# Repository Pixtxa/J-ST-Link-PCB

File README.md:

# J-ST-Link-PCB
Adapter PCB for connecting a programmer (SEGGER J-Link or STMicroelectronics ST-Link) to a microcontroller via jumper cables or 10 pin header.
It's also possible to monitor the target supply by LED or supply the target (with voltage regulator) or do both, when a 3 way jumper is used.
Because of this, Vtarget is called VCC.

<br>

## Schematic

## Components
Not all components are needed.
Some footprints can be used in multiple ways.
Some options cancel out each other.

Plan and solder what you need for your case.

### Examples

When using a keyed 20-pin female header, it fits nicely on J-Link base and ST-Link/V2.
A 6-pin female header can be soldered on the side to also support the nucleo ST-Link boards and it will still nicely fit on the J-Link Base, but not so nice on the ST-Link/V2.
Instead of the 20-pin female header, a male connector can be used. In this case (or if completely unused) it's possible to solder the Nucleo connector straight down.
It's only needed to solter the parts for the needed paths.
If the 3.3V regulator is unused (ST-Link provides 3.3 V; some targets are compatible with 5 V from J-Link), there is a solder jumper where the regulator would sit to bypass the pad.
Some other connecors are also avialable as female version; there are also angled connectors that might be better for some applications.
The pinout of the 10 pin connectors can be modified by some solder jumpers.
When ordering PCBs you mostly will get some more for a cheap price, so I reccomend to assemble different versions for different applications and maybe use different colored parts.

### Connectors
- 20 pin header
  - For standard ST-Link or J-Link
  - Can be soldered as male connector on top side for connecting to a cable
  - Can be soldered as female connector on bottom side for connecting directly to the programmer
    - PCB dimensions are designed for this usage with ST-Link/V2 and J-Link Base
    - I've found them as [2.54 mm pitch 20 pin female header with polarizing key, wide type on AliExpress](https://www.aliexpress.com/item/32956131069.html?spm=a2g0o.order_list.order_list_main.14.36e81802jonIUv)
  - Pinout is mostly [JTAG Interface Connection](https://www.segger.com/products/debug-probes/j-link/technology/interface-description/) with changes for ST-Link:
    - Pin 1+2: Bridged together (some ST-Link need both wired together for cable detection or something while pin 2 is unused on J-Link, so connecting them seems fine)
    - Pin 4: UART RX (ST-Link)
    - Pin 6: UART TX (ST-Link)
    - Pin 8: Boot0 (ST-Link)
    - Pin 10: SWIM (ST-Link)
    - Pin 14: SWIM_nRST (ST-Link)
- 6 pin header
  - Designed to be compatible with [CN4 of the break away ST-Link on STM32 nucleo boards](https://ehelectronics.wordpress.com/2015/12/05/stm32-nucleo-and-st-link/)
  - Can be soldered straight down to sit nicely above the Nucleo ST-Link
  - Can be soldered to the side to be combined with the 20 pin female header and will still fit nicely on the J-Link base
  - Pin 1-4 can be used with pogo pins [for programming hoverboards (SWD Programming Header)](https://github.com/lucysrausch/hoverboard-firmware-hack)
- Two 10 pin headers
  - 1.27 mm pitch version for connecting directly to my targets
    - I've found them as [1.27mm pitch SMD male shrouded box header on AliExpress](https://www.aliexpress.com/item/32951697063.html?spm=a2g0o.order_list.order_list_main.40.36e81802jonIUv) and [on Mouser](https://my.mouser.com/ProductDetail/Amphenol-FCI/20021521-00010C1LF?qs=pLQRQR43dtoQtFgybK4DSw%3D%3D)
  - 2.54 mm pitch version for other targets, Tag connect or other adapters
  - Both connectors share the same pinout
    - It's designed to be compatible with [the PCB-side connector of the 10-Pin Needle Adapter](https://www.segger.com/products/debug-probes/j-link/accessories/adapters/10-pin-needle-adapter/) and ARM 10 pin JTAG/SWD
    - Pin 5, 7 and 9 are [configurable via solder jumpers](https://github.com/Pixtxa/J-ST-Link-PCB#jumpers)
- Three pin headers on top
  - Can be used for connecting jumper cables
  - Can be used to solder wires directly on
  - STM8 SWIM
    - For SWIM programming with ST-LINK/V1, maybe also /V2
    - Used by STM8 microcontrollers
    - Implemented but untested
  - STM32 SWD
    - For SWD programming with J-Link and ST-Link
    - Used by STM32 Microcontrollers
  - UART
    - ST-Link features UART somehow, so this might be interesting for debugging or programming ESP8266 or ESP32
    - Implemented but untested

### Jumpers
- J1
  - NC*: Don't monitor/supply VCC - VCC is only connected to the programmer
  - LEFT+MIDDLE: Monitor VCC - VCC is connected to the programmer and an LED (if LED + resistor is assembled)
  - MIDDLE+RIGHT: Supply VCC - VCC is connected to the programmer and the supply voltage (if voltage regulator is assembled or J3 is set)
  - LEFT+MIDDLE+RIGHT: Monitor and supply VCC - combination of the last two options above
- J3
  - NC*: Use voltage regulator for supply voltage
  - SET: Skip voltage regulator, wire Pin 19 (5 V on J-Link; 3.3 V on ST-Link) directly to J1
- J5
  - CON*: Connect Supply to pin 5
  - NC: Not connect anything to pin 5
  - GNC: Connect Ground to pin 5
- J7
  - CON*: Connect RTCK to pin 7
  - NC: Not connect anything to pin 7
  - GNC: Connect Ground to pin 7
- J9
  - CON*: Connect nTrst to pin 9
  - NC: Not connect anything to pin 9
  - GNC: Connect Ground to pin 9
* = default

### LED + Resistor
- Only lights up if J1 is selected to monitor VCC and there is voltage on VCC
- Both 0603
- LED color doesn't really matter, chose what you like, but make sure it works with your target voltage (usualy red works with lowest voltage)
- Resistor value depends on LED and target voltage, but 330...1000 Ω should be fine for most LEDs

### Voltage regulator + capacitors
- Designed for 3.3 V via TLV70433 with 100n 0603 capacitors
- Only needed for powering 3.3 V targets on J-Link, which outputs 5 V
  - ST-Link already outputs 3.3 V and doesn't need it
  - Because of TLV70433 has a low voltage drop, it's possible for most 3.3 V targets to assemble the regulator and use this PCB on J-Link and ST-Link 
- Other voltage regulators (second source or for other voltage levels) might be compatible with this footprint
- If unused, J3 (located whrere the regulator would sit) can be set to bypass the regulator pad

## Tested
- Programmers
  - J-Link Base (SWD)
  - ST-Link/V2 (SWD)
- Microcontrollers
  - STM32C0 (SWD)
  - STM32F1 (SWD)
  - STM32L0 (SWD)
- Target Connectors
  - STM32 (SWD)
  - 10 pin 1.27 mm (SWD)
  - 10 pin 2.54 mm (SWD)

## Attribution
- Adafruit microbuilder and built in EAGLE libs are used together with own changes/modifications
- [EAGLE.gitignore by github](https://github.com/github/gitignore/blob/main/Eagle.gitignore)

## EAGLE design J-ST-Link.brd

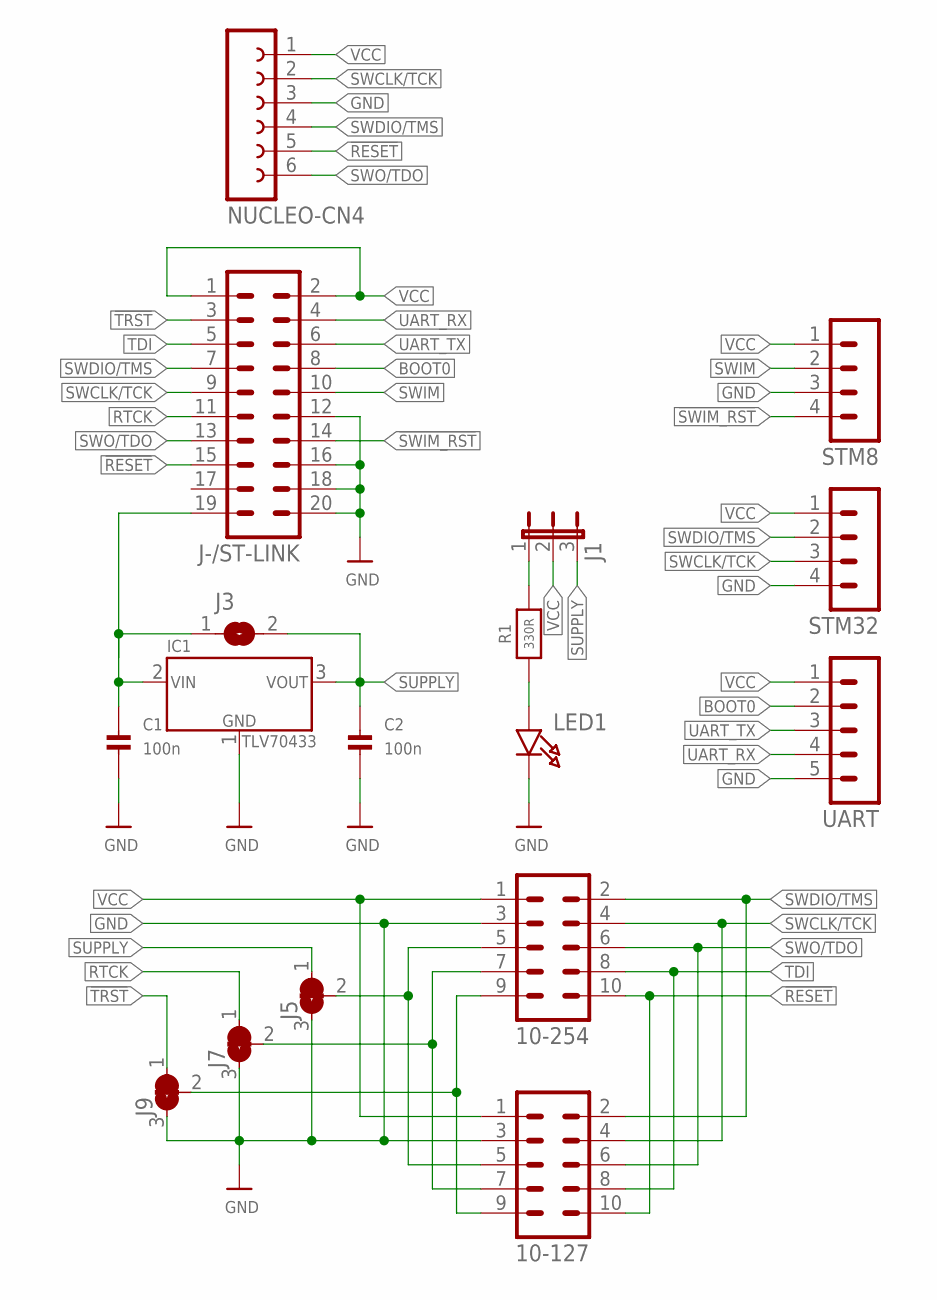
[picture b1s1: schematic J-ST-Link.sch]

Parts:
10-127: CON-HARTING-ML_ML10S
10-254: ML10
C1, C2: 100n; _0603MP
IC1: TLV70433; SOT23-5
J1: JUMPER3LONG; JUMPER3_LONG
J3: SOLDERJUMPERSMALL_NOPRINT; SOLDERJUMPER_SMALL_NOPRINT
J5, J7, J9: SOLDERJUMPER_2WAY_CLOSED; SOLDERJUMPER_2WAY_CLOSED_0603
J-/ST-LINK: ML20
LED1: LED0603_NOOUTLINE; CHIPLED_0603_NOOUTLINE
NUCLEO-CN4: FE06WSQUARE; FE06W_SQUARE
R1: 330R; 0603-NO
STM8, STM32: MA04-1
UART: MA05-1

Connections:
!RESET: 10-127.10, 10-254.10, J-/ST-LINK.15, NUCLEO-CN4.5
!SWIM_RST: J-/ST-LINK.14, STM8.4
!TRST: J9.1, J-/ST-LINK.3
BOOT0: J-/ST-LINK.8, UART.2
GND: 10-127.3, 10-254.3, C1.2, C2.2, IC1.1 (GND), J5.3, J7.3, J9.3, J-/ST-LINK.12, J-/ST-LINK.16, J-/ST-LINK.18, J-/ST-LINK.20, LED1.C, NUCLEO-CN4.3, STM8.3, STM32.4, UART.5
unnamed: LED1.A, R1.1
unnamed: J1.1, R1.2
RTCK: J7.1, J-/ST-LINK.11
RTCK/NC/GND: 10-127.7, 10-254.7, J7.2
SUPPLY: C2.1, IC1.3 (OUT), J1.3, J3.2, J5.1
SUPPLY/NC/GND: 10-127.5, 10-254.5, J5.2
SUPPLY_IN: C1.1, IC1.2 (IN), J3.1, J-/ST-LINK.19
SWCLK/TCK: 10-127.4, 10-254.4, J-/ST-LINK.9, NUCLEO-CN4.2, STM32.3
SWDIO/TMS: 10-127.2, 10-254.2, J-/ST-LINK.7, NUCLEO-CN4.4, STM32.2
SWIM: J-/ST-LINK.10, STM8.2
SWO/TDO: 10-127.6, 10-254.6, J-/ST-LINK.13, NUCLEO-CN4.6
TDI: 10-127.8, 10-254.8, J-/ST-LINK.5
TRST/NC/GND: 10-127.9, 10-254.9, J9.2
UART_RX: J-/ST-LINK.4, UART.4
UART_TX: J-/ST-LINK.6, UART.3
VCC: 10-127.1, 10-254.1, J1.2, J-/ST-LINK.1, J-/ST-LINK.2, NUCLEO-CN4.1, STM8.1, STM32.1, UART.1

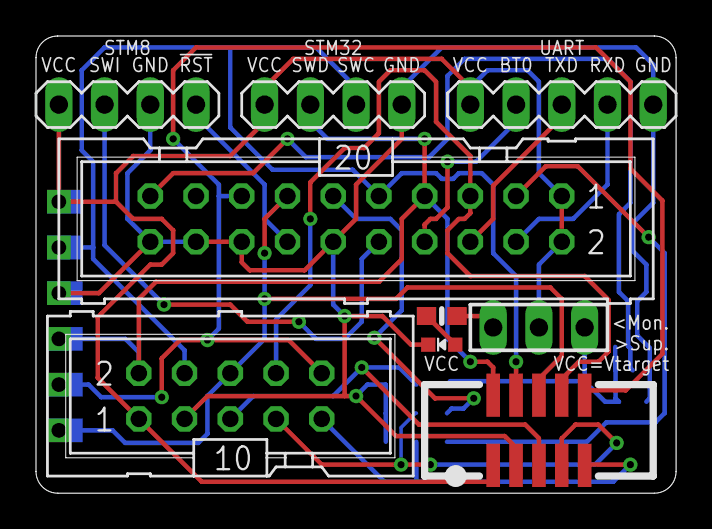
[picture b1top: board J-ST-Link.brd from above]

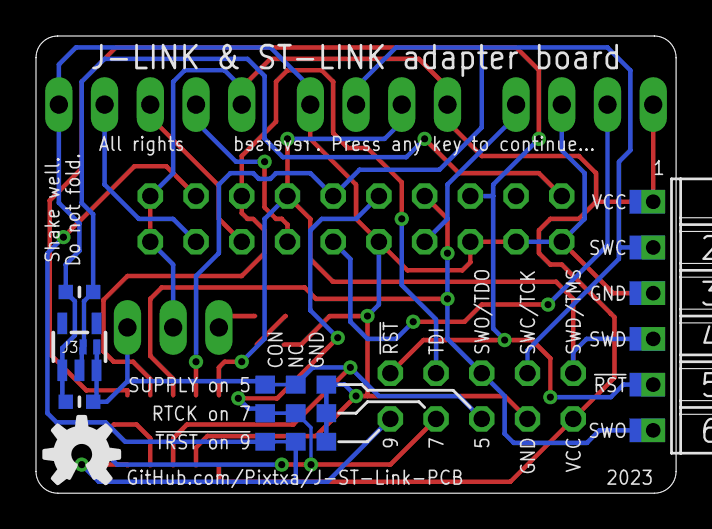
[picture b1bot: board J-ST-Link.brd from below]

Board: 2 copper layers, 35.6 x 25.4 mm, 17 parts (8 on the bottom side), 21 nets.

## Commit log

2023-10-09 HW-Rev V2
2023-10-09 Optimised routing
2023-10-09 Optimised schematic
2023-10-09 Added README.md
2023-10-09 Added LICENSE
2023-10-09 Added attribution
2023-10-09 Added gerber files for JLCPCB
2023-11-28 Update README.md
    Changed picture size
2023-11-28 Update README.md
    Changed picture size again
2024-01-21 Added brand names in readme.md

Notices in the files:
parts and their libraries:
microbuilder: This work is placed in the public domain, and may be freely used for commercial and non-commercial work with the following conditions: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
